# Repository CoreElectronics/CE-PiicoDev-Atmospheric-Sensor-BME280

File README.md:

# PiicoDev® Atmospheric Sensor BME280

This is the repo for the Core Electronics [PiicoDev Atmospheric Sensor BME280](https://core-electronics.com.au/catalog/product/view/sku/CE07503).

The PiicoDev® Atmospheric Sensor allows you to easily measure barometric pressure, humidity, and temperature. Use it to build your own weather station or perform experiments. Better still, you can connect to this sensor using our PiicoDev system - no soldering is required to connect the PiicoDev Atmospheric Sensor to other devices in the PiicoDev family.

**Features**

- Measure temperature, pressure and relative humidity
- PiicoDev connector, compatible with Qwiic and STEMMA QT (3.3V only)
- 2.54mm breakout for breadboarding/prototyping
- Manufactured and [supported](https://core-electronics.com.au/contacts/) in Australia by Core Electronics

**Technical Specifications**

- The BME280 measures
  - -40 to +85°C
  - 0 to 100% Relative Humidity
  - 300 to 1100 hPa
- Breakout connector: 3.3V SPI interface, 5V tolerant I2C interface (with pull-up resistors to 3.3V)

# License
This project is open source - please review the LICENSE.md file for further licensing information.

If you have any technical questions, or concerns about licensing, please contact technical support on the [Core Electronics forums](https://forum.core-electronics.com.au/).

# Attribution
The hardware design of this module is influenced by the design from [Sparkfun](https://github.com/sparkfun/Qwiic_Atmospheric_Sensor_Breakout_BME280).

*\"PiicoDev\" and the PiicoDev logo are trademarks of Core Electronics Pty Ltd.*

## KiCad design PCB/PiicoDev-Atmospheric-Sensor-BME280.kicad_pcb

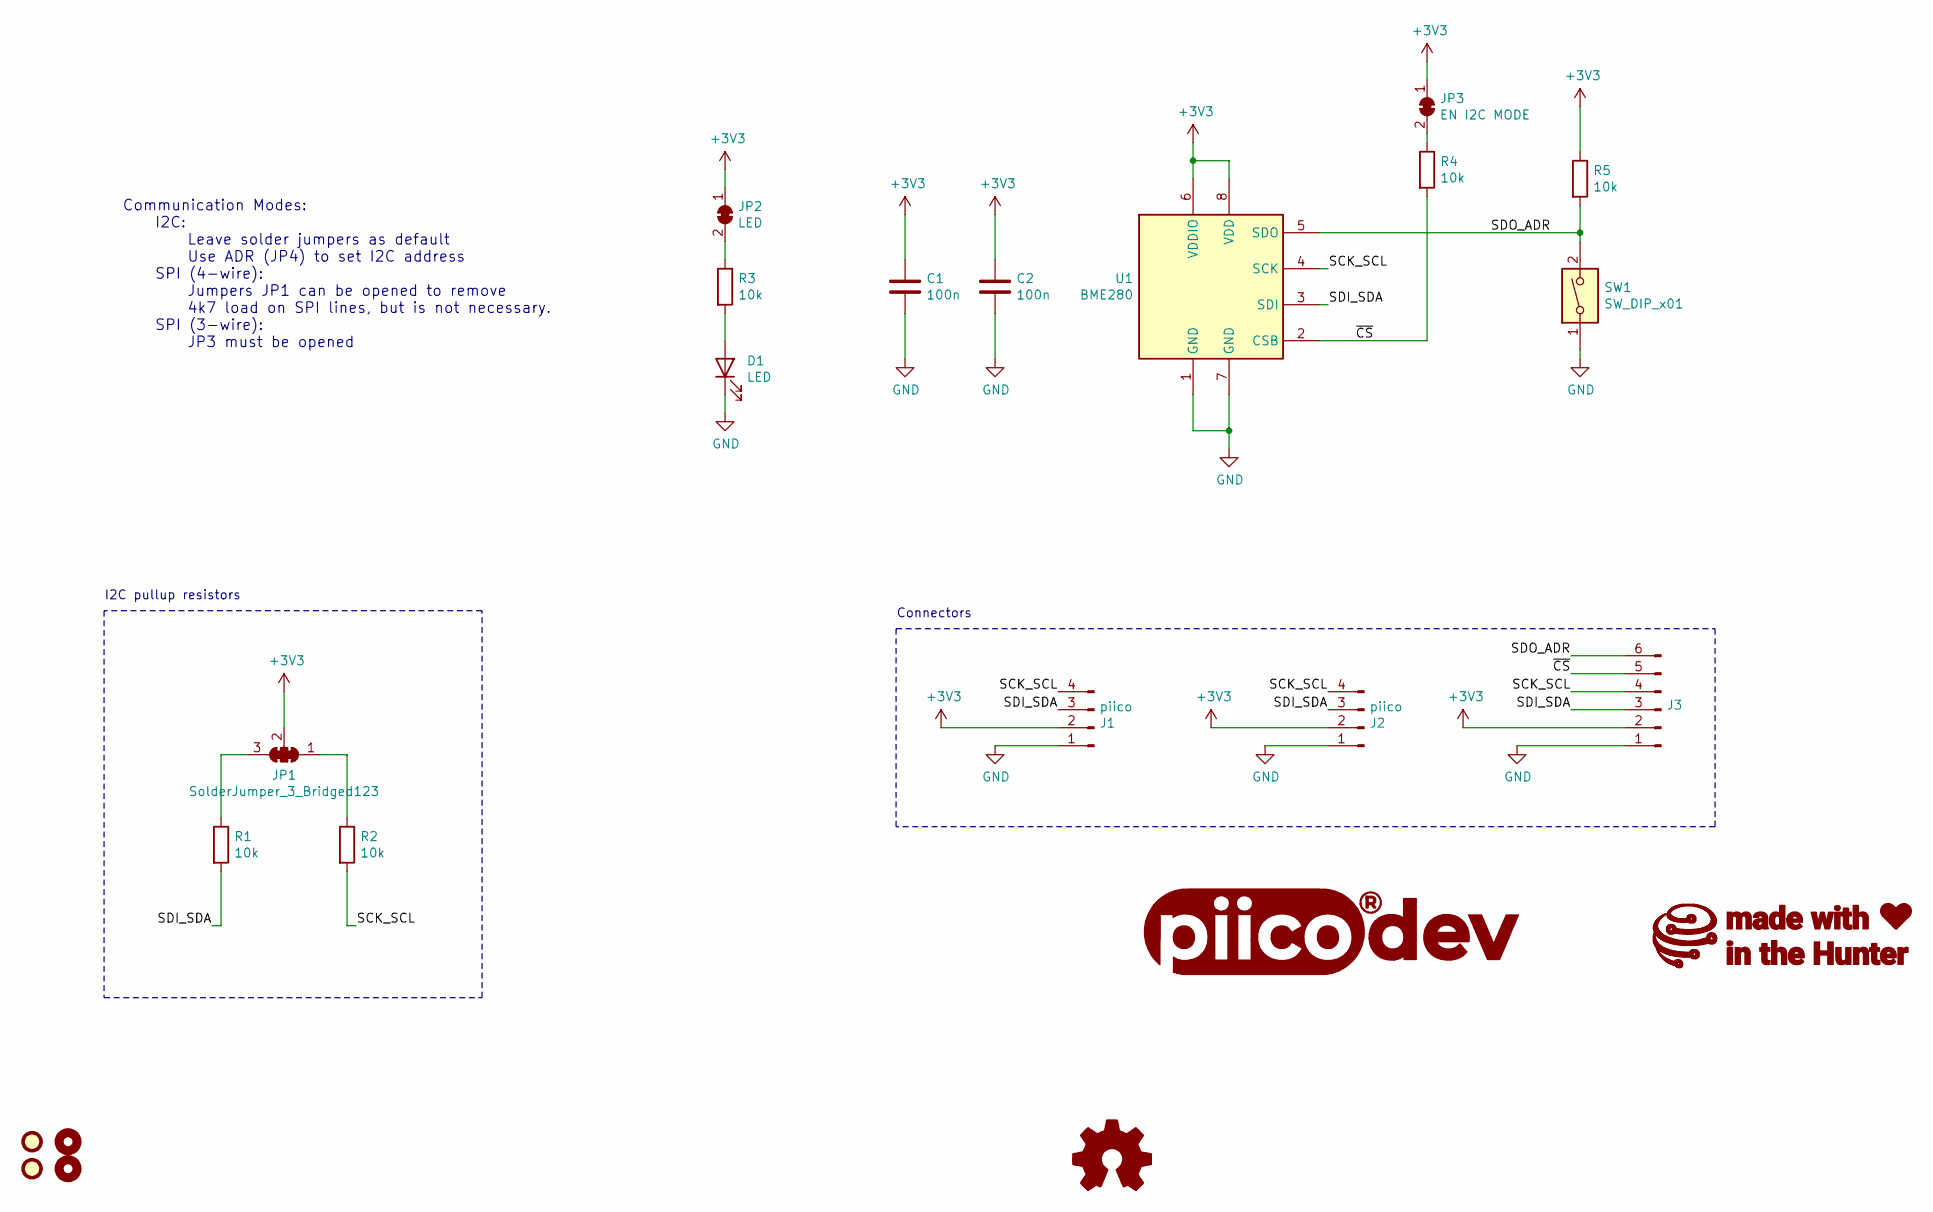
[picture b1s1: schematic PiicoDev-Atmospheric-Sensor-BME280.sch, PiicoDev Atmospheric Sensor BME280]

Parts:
C1, C2: 100n; C_0402_1005Metric
D1: LED; LED_0603_1608Metric
FID1, FID2: Fiducial; Fiducial_1mm_Mask2mm
G1: LOGO_CoreElectronics_no-text; CoreElectronics_logo_5mm
G2: LOGO_piico; piicodev_logo_14.2x3.4mm
G3: LOGO_made-with-love; piicodev_logo_14.2x3.4mm
H1, H2: MountingHole_2.7mm_M2.5
J1, J2: piico; JST_SH_SM04B-SRSS-TB_1x04-1MP_P1.00mm_Horizontal
J3: PinHeader_1x06_P2.54mm_Vertical_no-silk
JP1: SolderJumper_3_Bridged123; SolderJumper-3_P1.3mm_Closed_RoundedPad1.0x1.5mm_NumberLabe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
JP2: LED; SolderJumper-2_P1.3mm_Bridged_RoundedPad1.0x1.5mm
JP3: EN I2C MODE; SolderJumper-2_P1.3mm_Bridged_RoundedPad1.0x1.5mm
LOGO1: Logo_Open_Hardware_Small; oshw
R1, R2, R3, R4, R5: 10k; R_0402_1005Metric
SW1: SW_DIP_x01; SW_DIP_x01_Slide_CHS-01A1
U1: BME280; Bosch_LGA-8_2.5x2.5mm_P0.65mm_ClockwisePinNumbering

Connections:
+3V3: C1.1, C2.1, J1.2, J2.2, J3.2, JP1.2 (C), JP2.1 (A), JP3.1 (A), R5.1, U1.6 (VDDIO), U1.8 (VDD)
/SCK_SCL: J1.4, J2.4, J3.4, R2.2, U1.4 (SCK)
/SDI_SDA: J1.3, J2.3, J3.3, R1.2, U1.3 (SDI)
/SDO_ADR: J3.6, R5.2, SW1.2, U1.5 (SDO)
/~CS: J3.5, R4.2, U1.2 (CSB)
GND: C1.2, C2.2, D1.1 (K), J1.1, J2.1, J3.1, SW1.1, U1.1 (GND), U1.7 (GND)
unnamed: D1.2 (A), R3.2
unnamed: JP1.1 (A), R2.1
unnamed: JP1.3 (B), R1.1
unnamed: JP2.2 (B), R3.1
unnamed: JP3.2 (B), R4.1

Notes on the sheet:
Connectors
I2C pullup resistors
Communication Modes: I2C: Leave solder jumpers as default Use ADR (JP4) to set I2C address SPI (4-wire): Jumpers JP1 can be opened to remove 4k7 load on SPI lines, but is not necessary. SPI (3-wire): JP3 must be opened

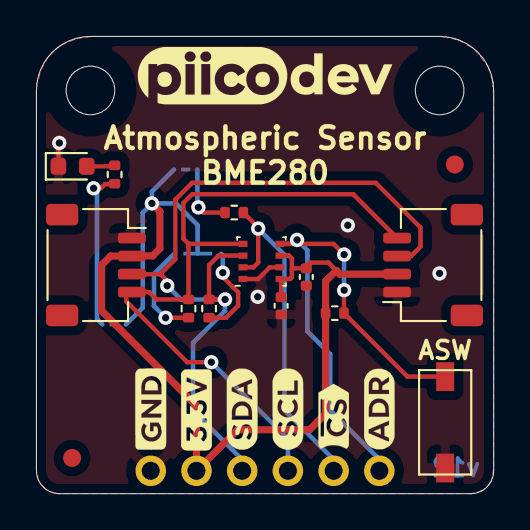
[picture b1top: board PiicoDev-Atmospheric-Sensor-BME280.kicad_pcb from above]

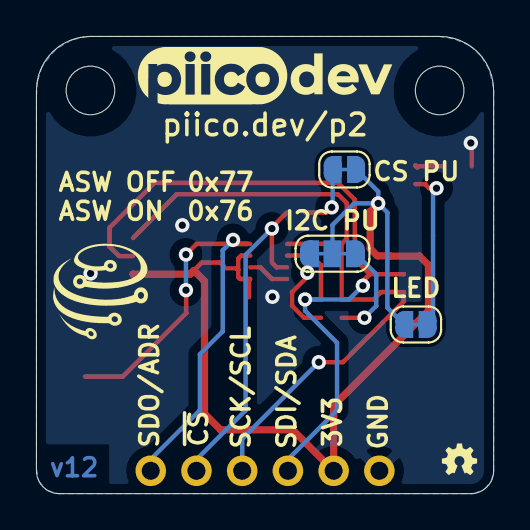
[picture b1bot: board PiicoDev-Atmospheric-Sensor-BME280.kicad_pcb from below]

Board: 2 copper layers, 25.4 x 25.4 mm, 24 parts (6 on the bottom side), 11 nets.

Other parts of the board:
G1#2: LOGO_CoreElectronics_made-with-love; piicodev_logo_14.2x3.4mm

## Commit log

2021-12-23 v11 Update
    Change resistor values
    Add DIP switch and remove ADR jumper
    Update graphic labels
    Remove solder mask between jumper pads
    Update text formatting
2022-01-06 Update PCB jumpers with thinner cut trace
2022-01-11 Rename address switch to ASW
2022-03-09 Update schematic to v12
2022-03-09 update image
2024-01-10 fix image URL

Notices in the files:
PCB/PiicoDev-Atmospheric-Sensor-BME280.kicad_pcb:
released under Creative Commons Share-alike 4.0 International
PCB/PiicoDev-Atmospheric-Sensor-BME280.sch:
https://creativecommons.org/licenses/by-sa/4.0/legalcode
